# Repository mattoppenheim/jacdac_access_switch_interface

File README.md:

Accessibility switch interface module for the Microsoft Jacdac project https://microsoft.github.io/jacdac-docs/.

The boards tested as working.

The board has two channels for interfacing accessibility switches or devices that can be controlled by an accessibility switch.

Each channel has a 3.5mm jack socket which can be configured either as an input or an output. This means that a switch can be connected to the board and used to operate Jacdac hardware, or that the module can act as a switch to control external devices or switchable software.

Each channel uses an opto-isolated relay to enable the board to pass enough current so that e.g. switchable toys can be operated.

To use the board as an output to control external hardware or software, use a double ended 3.5mm cable plugged into the 3.5mm socket.

Schematics and PCB layout are made using KiCad Version: 6.99.0-unknown-2887+gf4fa3b02c5+deb11, release build, running on Debian.

The board layout conforms with Ec30Template20x20 80-1.0 drawing.PDF. The Jacdac edge connector conforms with drawing JacdacEdgeConnectorRef 101-1.1 drawing.PDF.

Matthew Oppenheim 2023
matt@mattoppenheim.com

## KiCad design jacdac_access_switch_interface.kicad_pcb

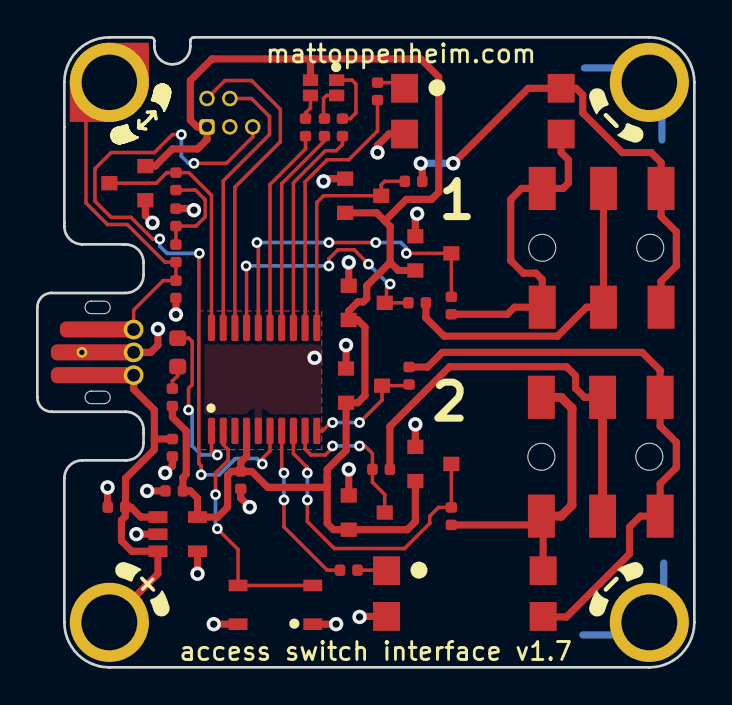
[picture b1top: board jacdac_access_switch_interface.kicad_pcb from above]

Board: 2 copper layers, 36.5 x 35.0 mm, 42 parts (0 on the bottom side), 34 nets.

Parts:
C1: 1uF, 10V; C_0402_1005Metric
C2: 1uF; C_0402_1005Metric
C3: 33pF; C_0402_1005Metric
C4: 0.1uF; C_0402_1005Metric
D1: RCLAMP0521P-N; D_0402_1005Metric
D2: RCLAMP0521-P; D_0402_1005Metric
D3, D4, D6, D7, D8, D9, D10: BAT54S; SOT-23
D5: LTST-C19HE1WT; LED_LTST-C19HE1WT
D12: LED_status; LED_0603_1608Metric
FB1: 1kOhm @ 100MHz; L_0402_1005Metric
J1: Conn_Jacdac_CardEdge; JD-PEC-02_Prerouted_recessed
J2: Conn_HackConnect; HackConnect_P1.27mm
J3, J4: jack_3.5_pj313d; jack_3.5_pj313d_smt
MH1: MountingHole_Pad; jacdac_hole_DATA_notched_MH1
MH2: jacdac_hole_GND_MH2
MH3: MountingHole_Pad; jacdac_hole_PWR_MH3
MH4: jacdac_hole_GND_MH4
R1: 220; R_0402_1005Metric
R2, R3: 330; R_0402_1005Metric
R4, R5, R9, R10, R11, R12: 10K; R_0402_1005Metric
R6: 150; R_0402_1005Metric
R7, R8: 33; R_0402_1005Metric
R13: 130; R_0402_1005Metric
SW1: SW_PTS810; SW_SPST_PTS810
U1: NCP114ASN330T1G; SOT-23-5
U2: STM32G030F6P6; TSSOP-20_4.4x6.5mm_P0.65mm
U3, U4: TLP240A; TLP240A_TP1_LF1

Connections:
+3V3: C2.1, C4.1, D3.2 (K), D4.2 (K), D5.4, D6.2 (K), D7.2 (K), D8.2 (K), D9.2 (K), D10.2 (K), J2.1 (Vcc), R13.1, U1.5 (OUT), U2.4 (VDD)
/JD_DATA: D1.1 (A1), FB1.2, J1.1 (JD_DATA), MH1.MH1
/JD_DATA_MCU: D3.3 (common), R1.1, U2.20 (PB3-6/USART1_TX)
/JD_STATUS: D12.1 (K), U2.1 (PB7/PB8)
/RELAY1: R3.2, U2.12 (PA5)
/RELAY2: R2.2, U2.7 (PA0)
/RGB_B: R8.2, U2.15 (PB0/PB1/PB2/PA8)
/RGB_G: R7.2, U2.14 (PA7)
/RGB_R: R6.2, U2.13 (PA6)
/RING1: J3.RING, R9.1
/RING1_P: D7.3 (common), R9.2, U2.17 (PA12[PA10])
/RING2: J4.RING, R12.1
/RING2_P: D10.3 (common), R12.2, U2.9 (PA2)
/SLEEVE1: J3.SLEEVE, R4.1, U4.4
/SLEEVE1_P: D4.3 (common), R4.2, U2.11 (PA4)
/SLEEVE2: J4.SLEEVE, R10.1, U3.3
/SLEEVE2_P: D8.3 (common), R10.2, U2.10 (PA3)
/SWDCLK: J2.4 (SWDCLK), U2.19 (PA15/PA14-BOOT0/SWCLK)
/SWDIO: J2.2 (SWDIO), U2.18 (PA13/SWDIO)
/TIP1: J3.TIP, R5.1, U4.3
/TIP1_P: D6.3 (common), R5.2, U2.16 (PA11[PA9])
/TIP2: J4.TIP, R11.1, U3.4
/TIP2_P: D9.3 (common), R11.2, U2.8 (PA1)
/nFLASH: SW1.2, U2.2 (PB9/PC14)
/nRESET: J2.5 (~RESET), U2.6 (PF2-NRST)
GND: C1.2, C2.2, C3.2, C4.2, D1.2 (A2), D2.2 (A2), D3.1 (A), D4.1 (A), D6.1 (A), D7.1 (A), D8.1 (A), D9.1 (A), D10.1 (A), J1.2 (GND), J2.3 (GND), MH2.MH2, MH4.MH4, SW1.1, U1.2 (GND), U1.4 (NC), U2.5 (VSS), U3.2, U4.2
JD_PWR: C1.1, D2.1 (A1), J1.3 (JD_PWR), MH3.MH3, U1.1 (IN), U1.3 (EN)
unnamed: C3.1, FB1.1, R1.2
unnamed: D5.1, R6.1
unnamed: D5.2, R7.1
unnamed: D5.3, R8.1
unnamed: D12.2 (A), R13.2
unnamed: R2.1, U3.1
unnamed: R3.1, U4.1

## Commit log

2022-05-04 v1.2 added opto-isolater, routing started
2022-05-04 Added 3dshapes and updated PCB
2022-05-11 v1.2 almost routed. Found error in connector placement.
2022-05-11 v1.3 started, board outline complete
2022-05-13 Replaced 3.5mm plug with 2x3.5mm sockets on schematic
2022-06-04 Component placement for 30x30 board
2022-06-04 Laying out 20x30mm board
2022-06-06 Placing components for 30x20mm pcb
2022-06-07 Components placed, ready for routing
2022-06-07 Setting up v1.5, combined input-output
2022-06-08 Moving footprint text from silkscreen to user comments
2022-07-08 Added input protection. Changed MCU to 20 pin STM32G031F6P6
2022-07-10 Replaced opto-isoltated relays with discrete FET relays
2022-07-20 Changed MCU to STM32G030F6P6, updated input protection resistor to 10K, updated audio symbol
2022-07-23 Updated audio socket symbol
2022-08-19 Added push button switch to enable flashing & orange status LED
2022-08-23 Initial component placement for PCB
2022-08-29 Updated footprint identifiers, routing started
2022-09-02 Routing in progress
2022-09-07 Last commit before re-assigning pins on MCU and spinning MCU
2022-09-07 Reassigned pins on MCU and spun MCU, routing ongoing
2022-09-14 Routing for PCB v1.7 complete
2022-09-14 Removing unused files from repository
2022-09-15 Added README.md
2022-09-23 v1.7 complete and sent for manufacture

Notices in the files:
jacdac_access_switch_interface.kicad_pcb:
Licence: Attribution 4.0 International (CC BY 4.0)
